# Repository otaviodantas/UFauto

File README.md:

**AUTOMAÇÃO DO AR CONDICIONADO**

Componentes usados:

- NodeMCU V1;
- Sensor DHT22;
- Led infravermelho;
- Display OLED 0.91;
- Transistor (a conferir);
- Resistor 2k ohm;
- Resistor 22 ohm;
- LDR;

O código pode conter alguns erros, estava em uma versão de transação para uma etapa futura.

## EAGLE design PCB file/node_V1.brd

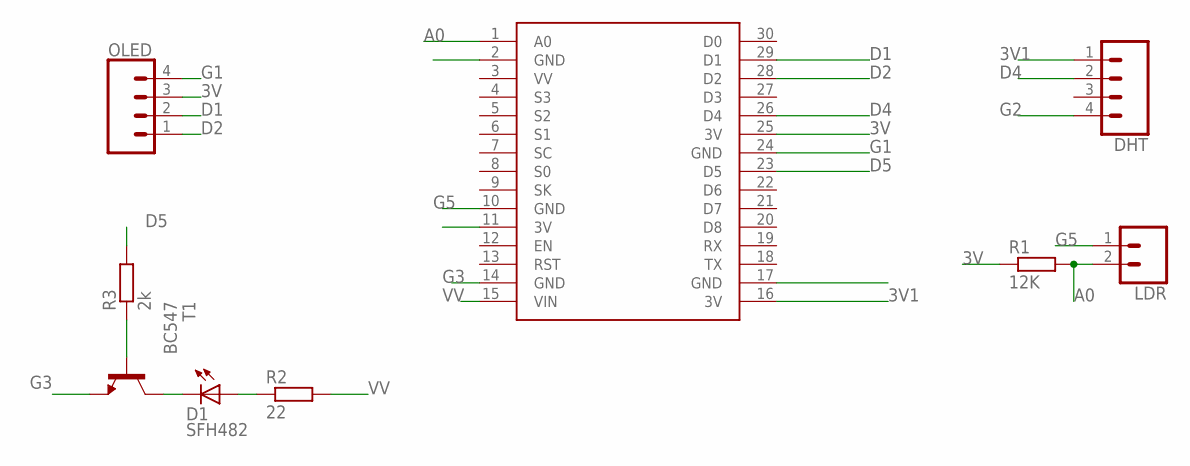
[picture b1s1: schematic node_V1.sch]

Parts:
D1: SFH482
DHT: CONN_04LONGPADS; 1X04_LONGPADS
LDR: CONN_02PTH3; 1X02_LONGPADS
OLED: CONN_04LONGPADS; 1X04_LONGPADS
R1: 12K; 0207/10
R2: 22; 0207/10
R3: 2k; 0207/10
T1: BC547; TO92
U$2: NODEMCU

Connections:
3V: OLED.3, R1.1, U$2.25 (3V)
3V1: DHT.1, U$2.16 (3V)
3V2: U$2.11 (3V)
A0: LDR.2, R1.2, U$2.1 (A0)
D1: OLED.2, U$2.29 (D1)
D2: OLED.1, U$2.28 (D2)
D4: DHT.2, U$2.26 (D4)
D5: R3.2, U$2.23 (D5)
G1: OLED.4, U$2.24 (GND)
G2: DHT.4, U$2.17 (GND)
G3: T1.1 (E), U$2.14 (GND)
G5: LDR.1, U$2.2 (GND), U$2.10 (GND)
unnamed: D1.K (C), T1.3 (C)
unnamed: D1.A, R2.1
unnamed: R3.1, T1.2 (B)
VV: R2.2, U$2.15 (VIN)

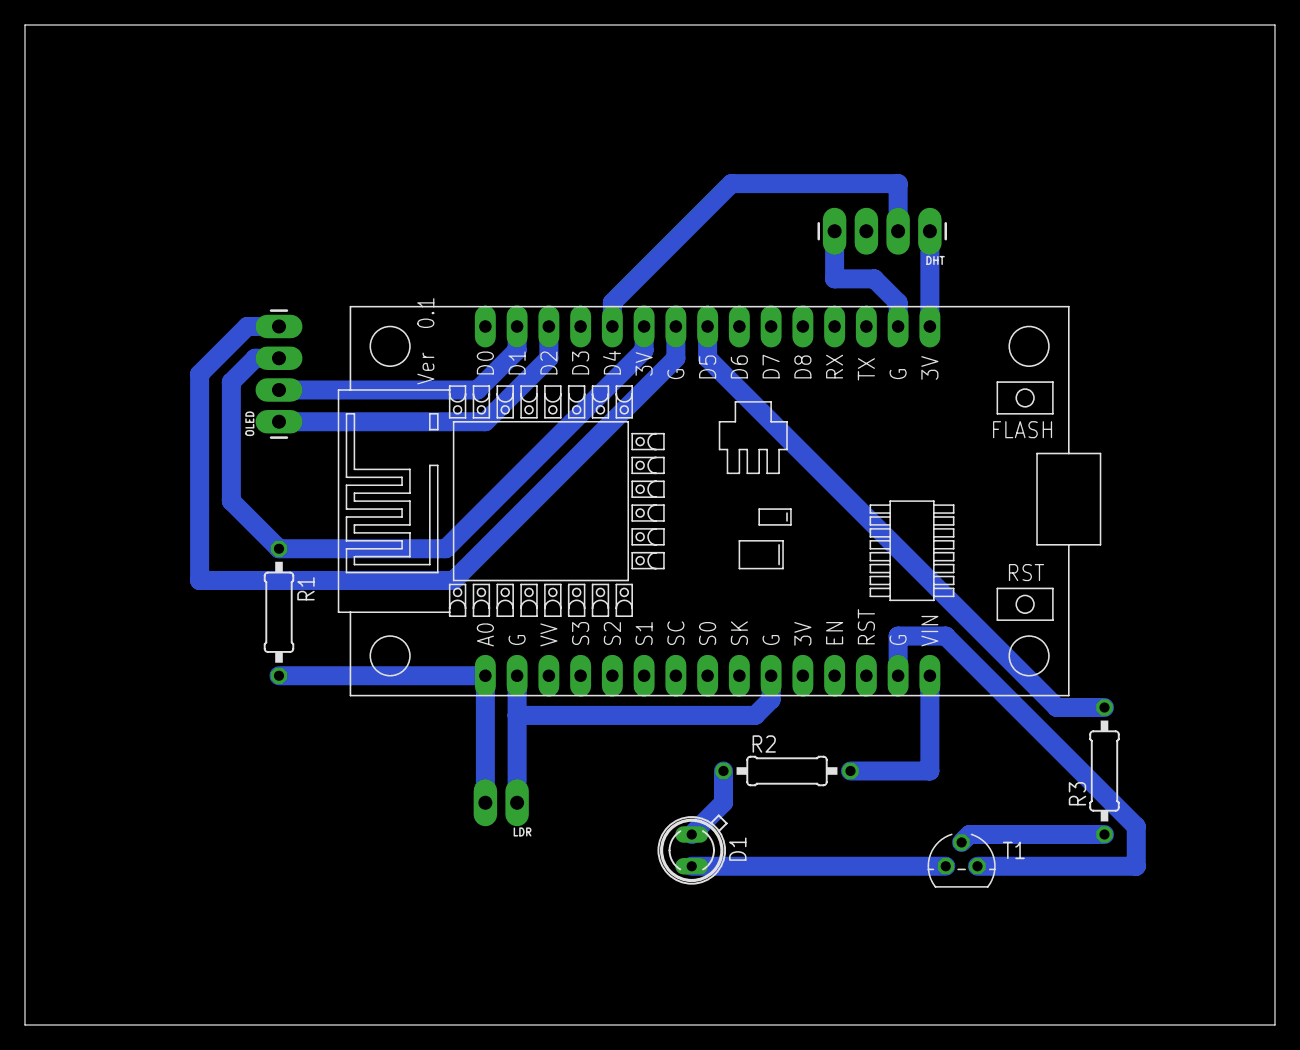
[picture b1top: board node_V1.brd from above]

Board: 2 copper layers, 100.0 x 80.0 mm, 9 parts (0 on the bottom side), 15 nets.

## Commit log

2019-11-12 Insert all files
2019-12-05 Code insert
    Open main code and delete file
2019-12-05 EAGLE FILE
    Eagle file for prototyping PCB
2019-12-05 INSERT LIBRARIES AND README

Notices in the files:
parts and their libraries:
SparkFun-Connectors: Licensing: Creative Commons ShareAlike 4.0 International - https://creativecommons.org/licenses/by-sa/4.0
